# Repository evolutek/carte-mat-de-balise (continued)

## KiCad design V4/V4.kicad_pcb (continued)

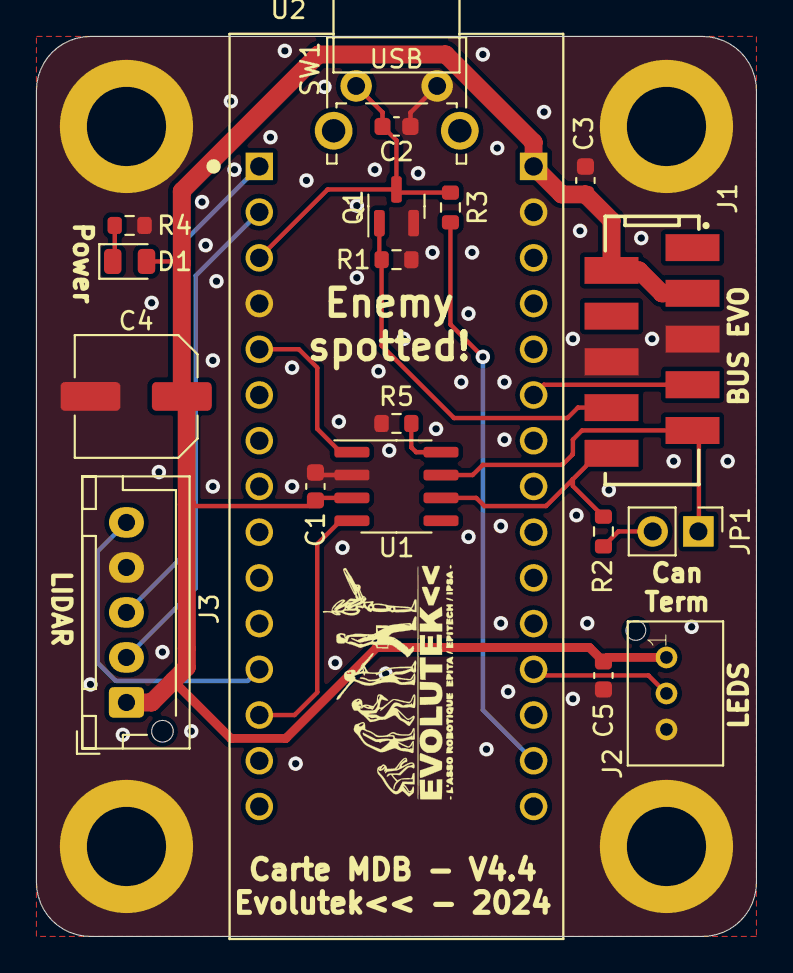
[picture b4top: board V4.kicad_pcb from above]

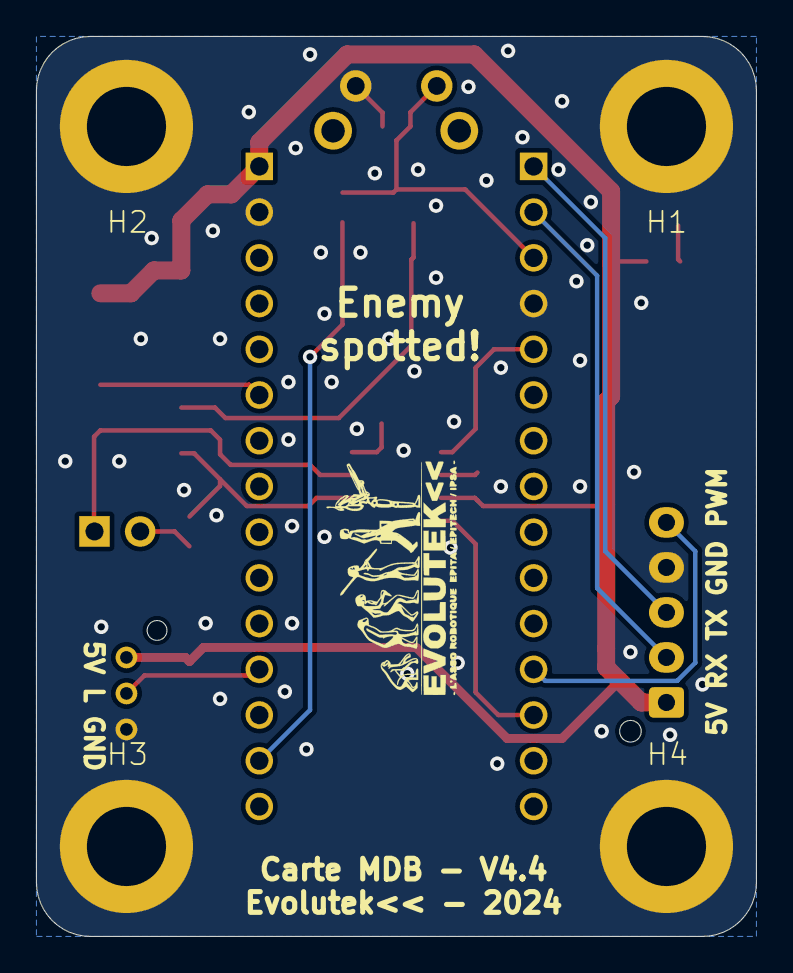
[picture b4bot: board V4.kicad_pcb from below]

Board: 2 copper layers, 40.0 x 50.0 mm, 24 parts (5 on the bottom side), 17 nets.

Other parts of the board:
Gr: LOGO; logo-evo-min

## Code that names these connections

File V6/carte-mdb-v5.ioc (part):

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Mcu.Name=STM32G491K(C-E)Ux
Mcu.Package=UFQFPN32
Mcu.UserName=STM32G491KEUx
PA0.GPIOParameters=GPIO_Label
PA0.GPIO_Label=IMU_NINT
PA0.Signal=GPXTI0
PA1.GPIOParameters=GPIO_Label
PA1.GPIO_Label=LIDAR_PWM
PA1.Signal=S_TIM2_CH2
PA10.GPIOParameters=GPIO_Label
PA10.GPIO_Label=SD_DETECT
PA10.Signal=GPXTI10
PA11.Mode=Device
PA11.Signal=USB_DM
PA12.Mode=Device
PA12.Signal=USB_DP
PA13.GPIOParameters=GPIO_Label
PA13.GPIO_Label=SWDIO
PA13.Mode=Serial_Wire
PA13.Signal=SYS_JTMS-SWDIO
PA14.GPIOParameters=GPIO_Label
PA14.GPIO_Label=SWCLK
PA14.Mode=Serial_Wire
PA14.Signal=SYS_JTCK-SWCLK
PA15.GPIOParameters=GPIO_Label
PA15.GPIO_Label=BUS_SCL
PA15.Mode=I2C
PA15.Signal=I2C1_SCL
PA2.GPIOParameters=GPIO_Label
PA2.GPIO_Label=VCP_TX
PA2.Mode=Asynchronous
PA2.Signal=LPUART1_TX
PA3.GPIOParameters=GPIO_Label
PA3.GPIO_Label=VCP_RX
PA3.Mode=Asynchronous
PA3.Signal=LPUART1_RX
PA4.GPIOParameters=GPIO_Label
PA4.GPIO_Label=SD_CS
PA4.Signal=GPIO_Output
PA5.GPIOParameters=GPIO_Label
PA5.GPIO_Label=SD_SCK
PA5.Mode=Full_Duplex_Master
PA5.Signal=SPI1_SCK
PA6.GPIOParameters=GPIO_Label
PA6.GPIO_Label=SD_MISO
PA6.Mode=Full_Duplex_Master
PA6.Signal=SPI1_MISO
PA7.GPIOParameters=GPIO_Label
PA7.GPIO_Label=SD_MOSI
PA7.Mode=Full_Duplex_Master
PA7.Signal=SPI1_MOSI
PA8.GPIOParameters=GPIO_Label
PA8.GPIO_Label=IMU_SDA
PA8.Mode=I2C
PA8.Signal=I2C2_SDA
PA9.GPIOParameters=GPIO_Label
PA9.GPIO_Label=IMU_SCL
PA9.Mode=I2C
PA9.Signal=I2C2_SCL
PB0.GPIOParameters=GPIO_Label
PB0.GPIO_Label=LEDS
PB0.Mode=PWM Generation2 CH2N
PB0.Signal=TIM1_CH2N
PB3.GPIOParameters=GPIO_Label
PB3.GPIO_Label=LIDAR_TX
PB3.Mode=Asynchronous
PB3.Signal=USART2_TX
PB4.GPIOParameters=GPIO_Label
PB4.GPIO_Label=LIDAR_RX
PB4.Mode=Asynchronous
PB4.Signal=USART2_RX
PB5.GPIOParameters=GPIO_Label
PB5.GPIO_Label=CAN_RX
PB5.Mode=FDCAN_Activate
PB5.Signal=FDCAN2_RX
PB6.GPIOParameters=GPIO_Label
PB6.GPIO_Label=CAN_TX
PB6.Mode=FDCAN_Activate
PB6.Signal=FDCAN2_TX
PB7.GPIOParameters=GPIO_Label
PB7.GPIO_Label=BUS_SDA
PB7.Mode=I2C
PB7.Signal=I2C1_SDA
RCC.HSE_VALUE=8000000
RCC.SYSCLKFreq_VALUE=64000000
RCC.SYSCLKSource=RCC_SYSCLKSOURCE_PLLCLK
board=custom

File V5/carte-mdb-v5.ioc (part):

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Mcu.Name=STM32G491K(C-E)Ux
Mcu.Package=UFQFPN32
Mcu.UserName=STM32G491KEUx
PA0.GPIOParameters=GPIO_Label
PA0.GPIO_Label=LEDS
PA0.Signal=S_TIM2_CH1
PA1.GPIOParameters=GPIO_PuPd,GPIO_Label
PA1.GPIO_Label=AU
PA1.GPIO_PuPd=GPIO_PULLDOWN
PA1.Signal=GPIO_Input
PA10.GPIOParameters=GPIO_Label
PA10.GPIO_Label=LIDAR_RX
PA10.Mode=Asynchronous
PA10.Signal=USART1_RX
PA11.GPIOParameters=GPIO_Label
PA11.GPIO_Label=USB_D-
PA11.Mode=Device
PA11.Signal=USB_DM
PA12.GPIOParameters=GPIO_Label
PA12.GPIO_Label=USB_D+
PA12.Mode=Device
PA12.Signal=USB_DP
PA13.GPIOParameters=GPIO_Label
PA13.GPIO_Label=SWDIO
PA13.Mode=Trace_Asynchronous_SW
PA13.Signal=SYS_JTMS-SWDIO
PA14.GPIOParameters=GPIO_Label
PA14.GPIO_Label=SWCLK
PA14.Mode=Trace_Asynchronous_SW
PA14.Signal=SYS_JTCK-SWCLK
PA15.GPIOParameters=GPIO_PuPd,GPIO_Label
PA15.GPIO_Label=LIDAR_SELECT
PA15.GPIO_PuPd=GPIO_PULLDOWN
PA15.Signal=GPIO_Input
PA2.GPIOParameters=GPIO_Label
PA2.GPIO_Label=VCP_TX
PA2.Mode=Asynchronous
PA2.Signal=USART2_TX
PA3.GPIOParameters=GPIO_Label
PA3.GPIO_Label=VCP_RX
PA3.Mode=Asynchronous
PA3.Signal=USART2_RX
PA4.Mode=NSS_Signal_Hard_Output
PA4.Signal=SPI1_NSS
PA5.Mode=Full_Duplex_Master
PA5.Signal=SPI1_SCK
PA6.Mode=Full_Duplex_Master
PA6.Signal=SPI1_MISO
PA7.Mode=Full_Duplex_Master
PA7.Signal=SPI1_MOSI
PA8.GPIOParameters=GPIO_Label
PA8.GPIO_Label=LIDAR_PWM
PA8.Signal=GPIO_Output
PA9.GPIOParameters=GPIO_Label
PA9.GPIO_Label=LIDAR_TX
PA9.Mode=Asynchronous
PA9.Signal=USART1_TX
PB0.GPIOParameters=GPIO_PuPd,GPIO_Label
PB0.GPIO_Label=CD
PB0.GPIO_PuPd=GPIO_PULLUP
PB0.Signal=GPIO_Input
PB3.GPIOParameters=GPIO_Label
PB3.GPIO_Label=SWO
PB3.Mode=Trace_Asynchronous_SW
PB3.Signal=SYS_JTDO-SWO
PB4.GPIOParameters=GPIO_Speed,PinState,GPIO_Label
PB4.GPIO_Label=STATUS
PB4.GPIO_Speed=GPIO_SPEED_FREQ_HIGH
PB4.PinState=GPIO_PIN_RESET
PB4.Signal=GPIO_Output
PB5.GPIOParameters=GPIO_Label
PB5.GPIO_Label=CAN_RX
PB5.Mode=FDCAN_Activate
PB5.Signal=FDCAN2_RX
PB6.GPIOParameters=GPIO_Label
PB6.GPIO_Label=CAN_TX
PB6.Mode=FDCAN_Activate
PB6.Signal=FDCAN2_TX
PB7.GPIOParameters=GPIO_Label
PB7.GPIO_Label=LIDAR_LED
PB7.Signal=S_TIM3_CH4
RCC.HSE_VALUE=8000000
RCC.SYSCLKFreq_VALUE=64000000
RCC.SYSCLKSource=RCC_SYSCLKSOURCE_PLLCLK
board=custom

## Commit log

2019-06-30 Add Lib
2019-06-30 Add V1 schematics
2019-07-02 Add .gitignore and clean repo
2019-07-02 Complete lib
2019-07-02 Complete design
2019-07-02 Add CAM files
2019-07-02 Add Documentation
2019-07-02 Push managed lib
2019-08-31 Update Res value
2019-09-12 Re-route properly the board
2019-09-13 Add Arduino test code
2019-09-16 Add code to control leds
2019-09-16 Control leds with sensors
2019-09-16 Move libs into sub-folder
2019-09-16 Correct board size and prepare to be route
2019-09-16 V1 routed
2019-09-16 Add code to use N sensors with leds
2019-09-17 Change board size and add BOM
2019-09-24 Make code init each sensors with xshut pin
2019-10-04 Remove old files
2020-01-18 Adding library for MCP23017-E_SP
2020-01-18 Add schematic for V2, change to MCP23017
2020-01-18 Add NSensors with support for mcp23017 xshut only (no interrupt)
2020-01-18 [V2] Add schematic and gerber pdf
2020-01-19 [V2] Release with two Gpio Expander
2020-01-24 Add scr file to gitignore (bitmap import tmp file)
2020-01-24 Standarized resistance value and fix power symbol
2020-01-24 Update schematic pdf
2020-01-24 [V.2] Release
2020-01-25 [V2.0] Change MCP placement
2020-02-26 [add] function for mat-balise
2020-03-02 [V2.1] Routes RESET on VCC and add a capacitor
2020-03-02 Rename Python directory
2020-03-29 [V2.2] Realase V2.2 with a RESET Button
2020-04-25 Update Arduino code
2020-04-25 Remove useless code
2020-05-15 Add continuous mode and measure ellipsed time for a scan
2020-08-20 Add V3.0
2020-08-20 WIP teensy
2020-08-21 [V3.0] Release V3.0 with a teensy
2020-08-23 Add Teensy code for MDB with basi communication
2020-08-24 MDB Teensy i2c communication
2020-09-01 MDB Teensy
2020-09-01 Error mode improvements
2020-09-01 Setup now checks all sensors
2020-09-03 [V3.2] Release V3.2
2020-09-15 Teensy now defaults to error to detect I2C problems
2020-10-01 More robust MDB code
2020-10-05 Fixed MDB sensors initialisation problem + Waiting mode
2020-10-09 Small fixes TeensyMDB
2020-10-16 Forgot to process n and f commands
2020-10-18 Teensy code improvements
2020-10-21 Error mode blinks in red
2020-10-22 Coefs on sensors to trigger avoid
2020-12-08 Add V4
2021-02-14 V4.1: Removed switch and deco 5V nucleo
2021-02-19 The Nucleo can control the Lidar :)
2021-02-19 Oops failed to push correctly
2021-02-19 Fixes
2021-02-22 Prepare V4.1 for fabrication
2021-02-24 Graphics fixes
2021-02-27 Testing Lidar communication from Nucleo
2021-04-27 Not working POC for Lidar on STM32
2021-12-07 Update V4 board Bus Evo
2023-03-07 Wip V4.3
2023-03-08 Release V4.3
2024-01-06 Carte MDB V4.4
2024-01-22 Replace smd spacer
2024-06-03 feat: first version with rplidar_clib
2024-10-25 Add Carte Led V1.0
2024-10-29 WIP V5
2024-11-04 Release V5.0
2024-11-14 Minor fixes
2024-11-30 feat: mda activate
2024-11-30 fix: change defines
2024-12-05 wip(dma): unstable com with dma
2024-12-05 fix(gitignore): remove Eclipse CDT project files section
2024-12-09 wip: dma tests
2024-12-09 wtf, remove please
2025-01-02 Add CAN ID label
2025-01-27 feat: project creation
2025-01-28 feat: add io.c, rplidar
2025-02-03 wip: HAL_UART_Receive receive only 1 byte
2025-02-03 fix: add receive in new_req function
2025-02-03 end: dma mandatory
2025-02-24 wip(dma): 1st received trame in idle dma
2025-03-17 feat: stable dma ! I REPEAT THE DMA IS STABLE !! one more time THE DMA IS STTTAAAABBBLLLEEEE !!!
    you didn't hear ?
    DMA STABLE !
    what did I said ?
    DMA STABLE !
    wat ?
    STABLE DMA !
2025-04-13 feat: dmaBuffer to circularBuffer
2026-03-10 Creation du projet V6
    - ajout IMU
    - passage du connecteur en Sous-bus Evo
    - passage du connecteur en USB C
    Todo: assignation des pins
2026-03-12 update ioc
2026-03-12 debut routage apres assignation pin
2026-03-14 progression routage cuivre (todo: DRC + serigraphie)
2026-03-14 fin du routage (TODO: review et prod-file)
2026-03-22 Correction CAN FD and USB
    fixed USB inversion
    changed SOIC8 CAN transceiver to CAN FD transceiver.
2026-03-30 Generate output
